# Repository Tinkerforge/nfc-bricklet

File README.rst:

NFC Bricklet
============

This repository contains the firmware source code and the hardware design
files. The documentation generator configs can be found at
https://github.com/Tinkerforge/generators

Repository Content
------------------

software/:
 * examples/: Examples for all supported languages
 * build/: Compiled files
 * src/: Source code of firmware
 * Makefile: Makefile to build project

hardware/:
 * Contains KiCad project files and additionally schematics as PDF

datasheets/:
 * Contains datasheets for sensors and complex ICs that are used

Hardware
--------

The hardware is designed with the open source EDA Suite KiCad
(http://www.kicad.org). Before you are able to open the files,
you have to install the Tinkerforge kicad-libraries
(https://github.com/Tinkerforge/kicad-libraries). You can either clone
them directly in hardware/ or clone them in a separate folder and
symlink them into hardware/
(ln -s kicad_path/kicad-libraries project_path/hardware). After that you
can open the .pro file in hardware/ with KiCad and from there view and
modify the schematics and the PCB layout.

Software
--------

If you want to do your own Brick/Bricklet firmware development we highly
recommend that you use our build environment setup script and read the
tutorial (https://www.tinkerforge.com/en/doc/Tutorials/Tutorial_Build_Environment/Tutorial.html).

To compile the C code we recommend you to install the newest GNU Arm Embedded
Toolchain (https://launchpad.net/gcc-arm-embedded/+download).
You also need to install bricklib2 (https://github.com/Tinkerforge/bricklib2).

You can either clone it directly in software/src/ or clone it in a
separate folder and symlink it into software/src/
(ln -s bricklib_path/bricklib2 project_path/software/src/). Finally make sure to
have CMake installed (http://www.cmake.org/cmake/resources/software.html).

After that you can build the firmware by invoking make in software/.
The firmware (.zbin) can then be found in software/build/ and uploaded
with brickv (click button "Flashing" on start screen).

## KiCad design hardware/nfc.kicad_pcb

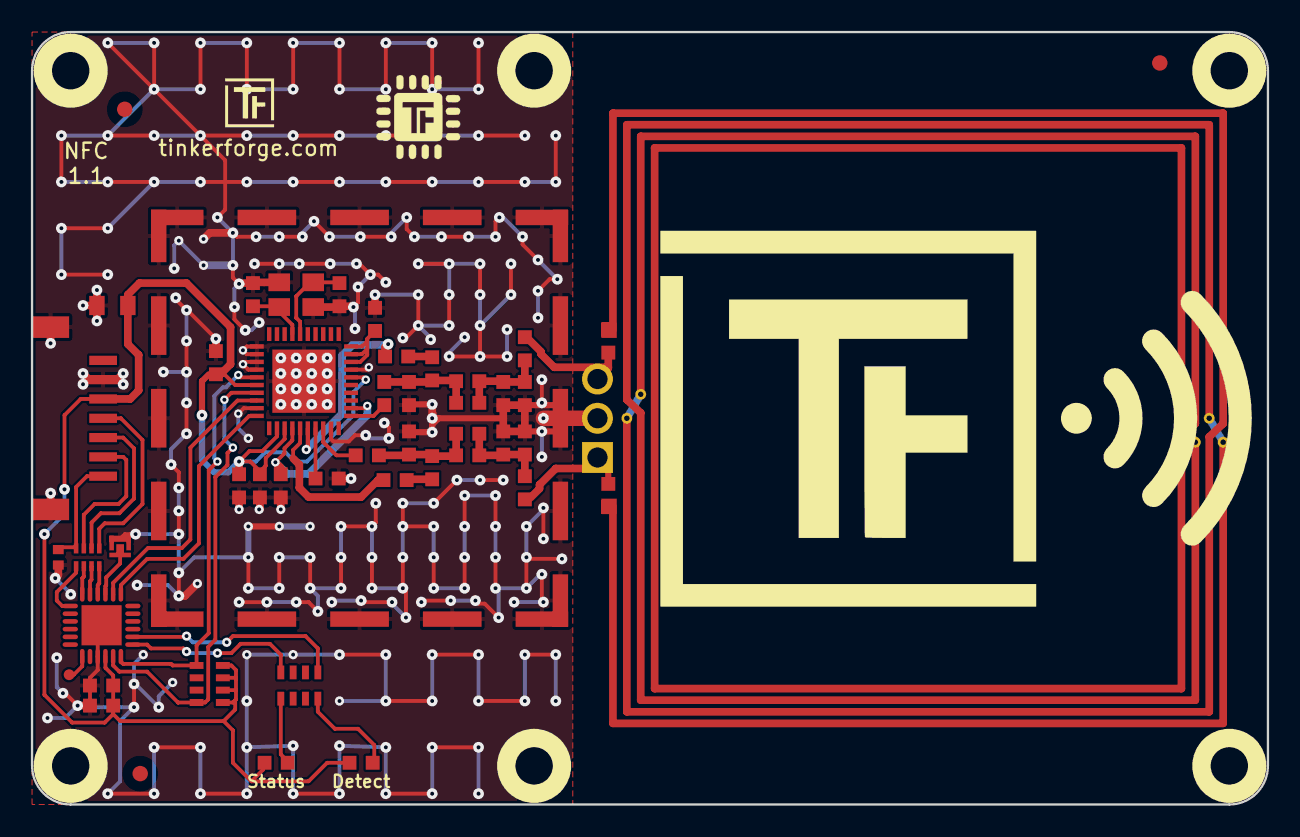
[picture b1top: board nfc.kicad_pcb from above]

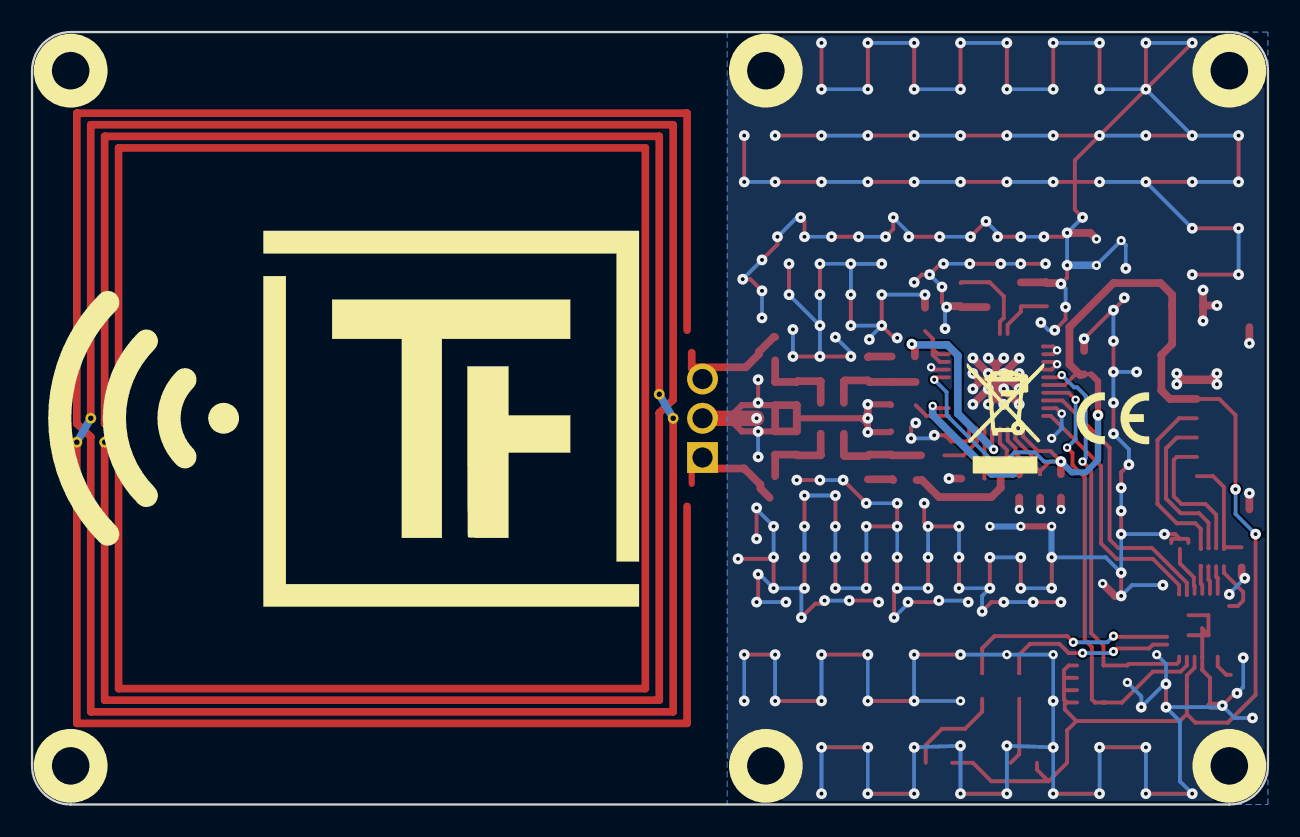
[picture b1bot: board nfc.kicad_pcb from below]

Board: 2 copper layers, 80.0 x 50.0 mm, 57 parts (2 on the bottom side), 39 nets.

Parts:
ANT1: PCB_ANTENNA; NFC_ANTENNA_40_40
C1: 220pF; C0402F
C2: 10uF; C0805
C3, C7, C10, C12: 1uF; C0603F
C4, C9, C13: 100nF; C0603F
C5, C6: 10pF/50V; C0603F
C8: 4.7uF; C0603F
C14, C15: 1nF/16V; C0603F
C16, C17: 680pF; C0603F
C18, C21: 56pF; C0603F
C19, C20: 22pF; C0603F
C22, C23: 120pF; C0603F
C24, C25: 2.2pF; C0603F
D1: blue; D0603F
D2: green; D0603F
Fiducial_Mark: VAL**; Fiducial_Mark
Fiducial_Mark#2, Fiducial_Mark#3: VAL**; Fiducial_Mark
J1: CONN_01X03; PIN_ARRAY_3X1
L1, L2: 160nH; R0603F
P1: CON-SENSOR2
P2: BOOT; SolderJumper
P3: DEBUG; DEBUG_PAD
R1, R2: 2.2k; R0603F
R3, R4: 1R5; R0603F
R5, R6: 0; R0603F
RP1: 82; 4X0402
RP2: 2.7k; 4X0603
RP3: 1k; 4X0603
SHD1: Shield; SHIELD-261_261
U1: XMC130024; QFN24-4x4mm-0.5mm
U2: PN7150; HVQFN40-6x6
U3, U4, U5, U6, U7, U8: DRILL; DRILL_NP
VAL: WEEE_7mm
VAL#2: CE_5mm
X1: 27.12MHZ; CRYSTAL_3225

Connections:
GND: C1.2, C2.2, C3.2, C4.2, C5.2, C6.2, C7.2, C8.2, C9.2, C10.2, C12.1, C13.2, C16.2, C17.1, C22.2, C23.1, C24.2, C25.1, J1.2, P1.2, P1.EP, P2.1, SHD1.1, U1.9, U1.EXP, U2.1, U2.2, U2.3, U2.4, U2.9, U2.19, U2.27, U2.EXP, X1.3
IRQ: U1.20, U2.8
unnamed: ANT1.1, R5.1
unnamed: ANT1.2, R6.1
unnamed: C1.1, P1.7, RP1.4
unnamed: C5.1, U2.37, X1.1
unnamed: C6.1, U2.36, X1.2
unnamed: C10.1, U2.28, U2.29, U2.30
unnamed: C12.2, U2.14, U2.22
unnamed: C13.1, U2.17
unnamed: C14.1, R1.2
unnamed: C14.2, U2.15
unnamed: C15.1, R2.2
unnamed: C15.2, U2.16
unnamed: C16.1, C18.1, C19.1, L1.2, R1.1
unnamed: C17.2, C20.1, C21.1, L2.2, R2.1
unnamed: C18.2, C19.2, C22.1, C24.1, R3.2
unnamed: C20.2, C21.2, C23.2, C25.2, R4.2
unnamed: D1.2, RP3.8
unnamed: D2.2, RP3.5
unnamed: J1.1, R3.1, R5.2
unnamed: J1.3, R4.1, R6.2
unnamed: L1.1, U2.18
unnamed: L2.1, U2.21
unnamed: P1.4, RP1.1
unnamed: P1.5, RP1.2
unnamed: P1.6, RP1.3
unnamed: P2.2, U1.21
unnamed: P3.1, U1.7
unnamed: RP3.1, U1.13
unnamed: RP3.4, U1.14
S-CLK: RP1.7, U1.23
S-CS: RP1.8, U1.22
S-MISO: RP1.5, U1.1
S-MOSI: RP1.6, U1.24
SCL: RP2.5, U1.11, U2.7
SDA: RP2.8, U1.12, U2.5
VCC: C2.1, C3.1, C4.1, C7.1, C8.1, C9.1, D1.1, D2.1, P1.3, RP2.1, RP2.2, RP2.3, RP2.4, U1.10, U2.6, U2.12, U2.13, U2.26
VEN: U1.19, U2.10

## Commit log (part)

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2017-08-01 Add gitignore
2017-08-01 Add datasheets
2017-08-01 Add tests
2017-08-01 Add initial test implementation
2017-08-01 Add missing ip_connection.py
2017-08-02 Add original NXP NfcLibrary
2017-08-02 Add swp and project files to gitignore
2017-08-04 Add pyc files to gitignore
2017-08-04 Add support for Ndef read/write
2017-08-04 Write ndef data directly into data buffer
2017-08-04 increase data buffer size to 8kb
2017-08-04 Remove temporary nfc lib debugging
2017-08-04 Remove debug prints
2017-08-04 use logging instead of uartbb
2017-08-09 Add support for > 255 byte ndef messages
2017-08-09 Remove old uartbb debug
2017-08-09 Add custom stack size
2017-08-09 Remove test blink task
2017-08-09 Add startup error logging
2017-08-09 Add support for type 3 and type 4 nfc tag read/write
2017-08-09 Add NFC datasheets
2017-08-09 Add more tests
2017-08-11 Use streaming function for Get Tag ID
2017-08-11 Rename TID to Tag ID
2017-08-14 Remove unused wdt import
2017-08-30 partial schematic of nfc bricklet
2017-08-31 partially routed
2017-09-04 fully routed
2017-09-04 add logos
2017-09-04 add shield hint
2017-09-20 fix shield grounding
2017-09-28 add status led, debug pad, boot pad
2017-09-28 add second led
2017-09-29 adapted to XMC1302 prototype board
    * XMC1403 -> XMC1302
    * bootstrapper, bootloader works
    * firmware untested
    * swap sda and scl in schematic
2017-09-29 add fiducials, swap sda,scl
2017-09-29 make vdd an island
2017-10-23 Add support for detection LED
2017-10-23 Add 3d information (tbc)
2017-10-25 fix shield description
2018-01-04 Add missing carriage return in debug messages
2018-01-04 Change NFC RF settings to conform to changes in linux_libnfc-nci library.
    See:
    * https://github.com/NXPNFCLinux/linux_libnfc-nci/issues/59
    * https://github.com/NXPNFCLinux/linux_libnfc-nci/commit/9b774ef656c22c4a14018c8916691bd708c95de5#diff-fca6cf6d5c39d91a1ec38e30f4956fa8
    We think that we were able to trigger the same bug as in issue 59.
2018-01-11 Show state transitions
2018-01-11 Make test robust
2018-01-11 Add Python examples
2018-01-12 Fix typo in Python examples
2018-01-12 Add Perl examples
2018-01-12 Fix typo
2018-01-12 Add Ruby examples
2018-01-15 Add PHP examples
2018-01-15 Add JavaScript examples
2018-01-15 Keep constants together
2018-01-17 Add Java examples
2018-01-18 Add C examples
2018-01-18 Simplify R/W type2 tag Ruby example
2018-01-18 Make R/W type2 tag example behaviour consistent
2018-01-18 Print message if detected tag type is not type-2
2018-01-18 Fix print message
2018-01-18 Make behaviour and state message output consistent
2018-01-18 Add MATLAB/Octave examples
2018-01-18 Simplify Python tag scan example
2018-01-19 Add C# examples
2018-01-19 Simplify write NDEF examples
2018-01-19 Add VB.NET examples
2018-01-19 Fix argument value
2018-01-22 Add Delphi/Lazarus examples
2018-01-30 Add 3d information (final)
2018-01-30 Fix 3d model
2018-01-30 Add 3d model (*.step & *.FCStd)
2018-02-12 Update example skeletons
2018-02-12 examples: Rename write-ndef to emulate-ndef
2018-02-16 Fix symbols (CONN_01X01)
2018-02-16 Add schematic PDF
2018-02-19 Remove unused interrupt control initialization
2018-02-19 Remove debug includes
2018-02-19 Turn off debug mode
2018-02-20 nxp_examples
2018-02-20 Cleanup KiCad libraries config
    Ensure LibDir=kicad-libraries and LibName1=tinkerforge.
    Remove special library.
2018-02-23 Use correct flash size (32kb)
2018-02-23 c: Avoid unused parameter warnings
2018-02-23 c: Fix variable declaration order
2018-02-23 c: Remove implicit const char* to char* cast
2018-02-23 delphi: Fix wrong function call
2018-02-23 python: Fix Python 3 synatx errors
2018-02-23 vbnet: Fix implicit cast warnings
2018-02-23 csharp: Fix varaible naming style
2018-02-28 javascript: Remove duplicated calls
2018-02-28 examples: Adapt to function name changes
2018-02-28 examples: Use constant
2018-02-28 Add new 3d model with more detailed components
2018-03-12 Add support for global maximum timeout
2018-03-12 Use correct spelling as generated (Ndef -> NDEF)
2018-03-12 Change state to Error-State in case of timeout in reader mode
2018-03-12 Add test for timeout, update bindings
2018-03-12 Increase versio number, add changelog
2018-05-11 Rename files
2018-05-24 perl: Use strict in examples
2018-06-07 fix led text
2018-06-18 Change capacitor footprint(s) to C0402F
2018-06-28 Fix readme
2018-07-11 Add Makefile with docker support
2018-07-11 Remove obsolete generate_makefile scripts
2018-07-11 Update directory structure and build instructions
2018-07-16 Remove symlink that was accidentially commitet
2018-08-31 Update changelog format
2018-10-01 Remove unused debug code
2018-10-01 Add support for stack size and HardFault debug
    By default turned off, but can now be commented in if needed
2018-10-01 Decrease coop stack size by 512 byte
    The 512 byte are nut needed by the coop task. This leaves a
    bit more space for the main thread.
2018-10-01 Make variables that are used in IRQ as well as main thread volatile
2018-10-04 Update changelog and version
2018-10-04 Fix date in changelog
2018-10-04 Add rev to changelog
2018-10-25 fix nfc pad clearances
2018-11-06 Add rust examples
2018-11-07 rust: Accept host names for ip connection, fix naming inconsistencies
2018-11-07 rust: Rename callback receivers.
2018-12-14 Add go examples.
2018-12-18 go: Change import path.
2018-12-18 go: Change import path again.
2018-12-20 rust: Reformat examples.
2019-01-24 mqtt: Add examples.
2019-01-24 mqtt: Remove executable bit in example permissions.
2019-01-24 go: Minor example fixes.
2019-01-24 Update user manual
2019-01-25 update 2.0.3 rev
2019-05-29 Add folders to .gitignore
2019-05-29 Increase version for new release (changes in bricklib2)
2019-08-22 c: Adapt to bindings changes
2020-01-14 examples: Use python3 input by default.
2020-03-17 java: Add missing comment
2020-03-17 Whitespace
2020-03-17 rust: Update to new skeleton
2020-04-03 Add openHAB examples.
2020-08-19 Add uc examples.
2020-08-25 uc: Adapt examples to new skeleton
2020-08-27 uc: Fix warnings.
2020-08-31 uc: Use fixed-with placeholders in format strings.
2020-09-02 uc: Add example driver note.
2021-01-28 Fix detection LED API return value
2021-01-28 Add rev for 2.0.5
2021-01-28 Fix year
2021-03-10 csharp: Whitespace
2021-05-20 Simplify, unify, clean up, fix and improve scan-for-tags examples
    The examples scan for tags forever now, instead of once.
2021-05-21 examples: Trigger tag ID request in all idle states
2021-05-21 javascript: Unify semicolon style
2021-05-21 vbnet: Fix tag ID formatting
2021-06-16 add nfc 1.1
    change board dimensions
2021-06-16 fix settings
2021-06-23 Make sure Nfc.h can be included multiple times
2021-06-23 Add -Os attributes, reorder struct elments, remove HF handler w/o logging
    We add some strategic -Os for specific functions that can save a lot
    of space and reorder the PH7150 struct to make access to specific
    elements in it more space efficient. This saves about 2k of flash in sum,
    enough to add the new "simple_tags" API.
2021-06-23 Add "simple tag" support
2021-06-23 Reuse simple_tag discovery function in cardemu, p2p and reader
2021-09-03 index = 255 => zero out simple tag data
2021-09-03 Add ref for v2.0.6
2021-09-23 csharp,vbnet: Fix tag ID format string
2021-09-23 javascript: Fix syntax errors and add missing scrolling
2021-09-23 javascript,vbnet: Add examples for new simple API
2021-10-25 Update KiCad link
    https://www.kicad.org/blog/2021/10/Avoid-links-to-former-kicad-domain/
2022-04-19 examples: uc: Rename TF_HalContext to TF_HAL.
2022-04-26 uc: Adapt to bindings changes
2022-07-06 Add license files.
2024-10-13 Update NfcLibrary from nxp
    This is step 1
    We will update the library in four steps.
    1. Overwrite the old library (including the one with changes) with the new library
    2. Fix stuff in port for XMC and fix general compile errors
    3. Add back the changes we had in the old version (if necessary)
    4. Add support for new stuff in the new library and improve library
2024-10-13 xmc_port: Always zero input buffer in receive function
    In some parts the NfcLibrary calls recv a with the same buffer
    until a specific answer is returend. In this case it could
    fill a buffer with stuff, then call recv again that comes out
    as a short read and then use part of the old data since the
    library never checks the "AnswerSize"
2024-10-13 Add back the NfcLibrary changes
    These are the changes we need to integrate NfcLibrary into
    the Bricklib code. The changes are the same that we had for
    the old version, just ported to the new Library version.
2024-10-13 Add define for type 5 tags (NFCV / ISO 15693)
2024-10-13 Add size checks to NxpNci_FillInterfaceInfo
    This function could be called with a corrupt pBuf before,
    which resulted in buffer overflows...
    TODO: Check if AnswerSize fits the expected data amount
    for the specific ModeTech.
2024-10-13 Don't use TIMEOUT_INFINITE
2024-10-13 Check for AnswerSize instead of comparing the pointer to 0
2024-10-13 Fix memset of tag_id_data (length 10 instead of 32)
2024-10-13 Add initial T5T and MIFARE ndef support
    currently only "simple mode" for Type 5 Tag implemented
2024-10-13 Make sure to zero the interface before calls that fill it
    Otherwise we might leak a uid into a newly detected tag
    that did not actually transfer a uid.
2024-10-13 Copy the tag id for each protocol case
    If we somehow get a NfcId for a tag that does not support it,
    we may copy a wrong id if we do it before the switch.
    If this problems happens it likely means something else went wrong
    beforehand, but this is an easy improvement anyway.
2024-10-13 Add some notes for tag types, technology and protocol standards
    This stuff is confusing every time i work with the code, now
    i can remind myself easily without search for everything all
    over again.
2024-10-13 Use -Os for complete project and remove T5T und MIFARE ndef support
    T5T should still work in simple mode, but currently we can't fit the
    new ndef support in the flash.
2024-10-13 Increase minor version
2024-10-13 Make sure to only copy NfcId if mode is poll and tech is NFCA
2024-10-13 Check for ISO 15693 tech in case of tag type 5
2024-10-14 Add cardemu listen modes and cardemu test
2024-10-14 Add .vscode folder to gitignore
2024-10-14 Change max tag id length from 32 to 10
2024-10-14 Add support for custom tag ID in cardemu mode
2024-10-15 Add support for more types
    we now additionally support:
    * NDEF read of Type 5 and Mifare Classic
    * NDEF write of Type 5 and Mifare Classic
    * Page read/write of Type 5
2024-10-15 Remove support for P2P for now
    tl;dr: No flash left for P2P, dropping it will have no impact
    since nobody uses it. Maybe we make a NFC Bricklet 2.0 in the
    future that has more flash and P2P enabled again.
    Currently the firmware does not fit into the flash anymore with
    the new support for Type 5 Tags and P2P enabled at the same time.
    Please note that P2P was mostly used to transfer data between
2024-10-17 Add changelog for version 2.1.0
2024-10-17 Add ref for version 2.1.0
2025-07-24 Add changelog entry for 2.1.1
2025-09-30 Make sure NFC Bricklet compiles with GCC 14
2026-01-26 Add Phone with HCE (host card emulation) as tag type
2026-01-27 Add date and ref for 2.1.2 release
2026-02-25 Fix typo in changelog

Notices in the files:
hardware/nfc.kicad_pcb:
Licensed under CERN OHL v.1.1
Copyright (©) 2021, B.Nordmeyer
Copyright Tinkerforge GmbH 2017.
This documentation describes Open Hardware and is licensed under the
CERN OHL v. 1.1.
